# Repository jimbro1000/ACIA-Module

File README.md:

# HD6309SBC ACIA MODULE #

This design provides a standard RS232 capability to the
HD6309SBC board. Available baud rates range from 50 to
115200.

## Interface ##

The board utilises mapped IO at address #xx0C to interact
with the primary processor. The R65C51 uart provides four
registers starting at this address.

The value of xx depends on the "mapped memory" signal line,
by default this is $FF00.

## Notes ##

The intended clock speed of the main SBC board is just over
3MHz which exceeds the limits of the original R65C51.
A slower clock speed would facilitate the use of the Rockwell
made components but it is highly recommended to use the WDC
version which will operate at much higher clock frequencies
(higher than the main clock can supply)

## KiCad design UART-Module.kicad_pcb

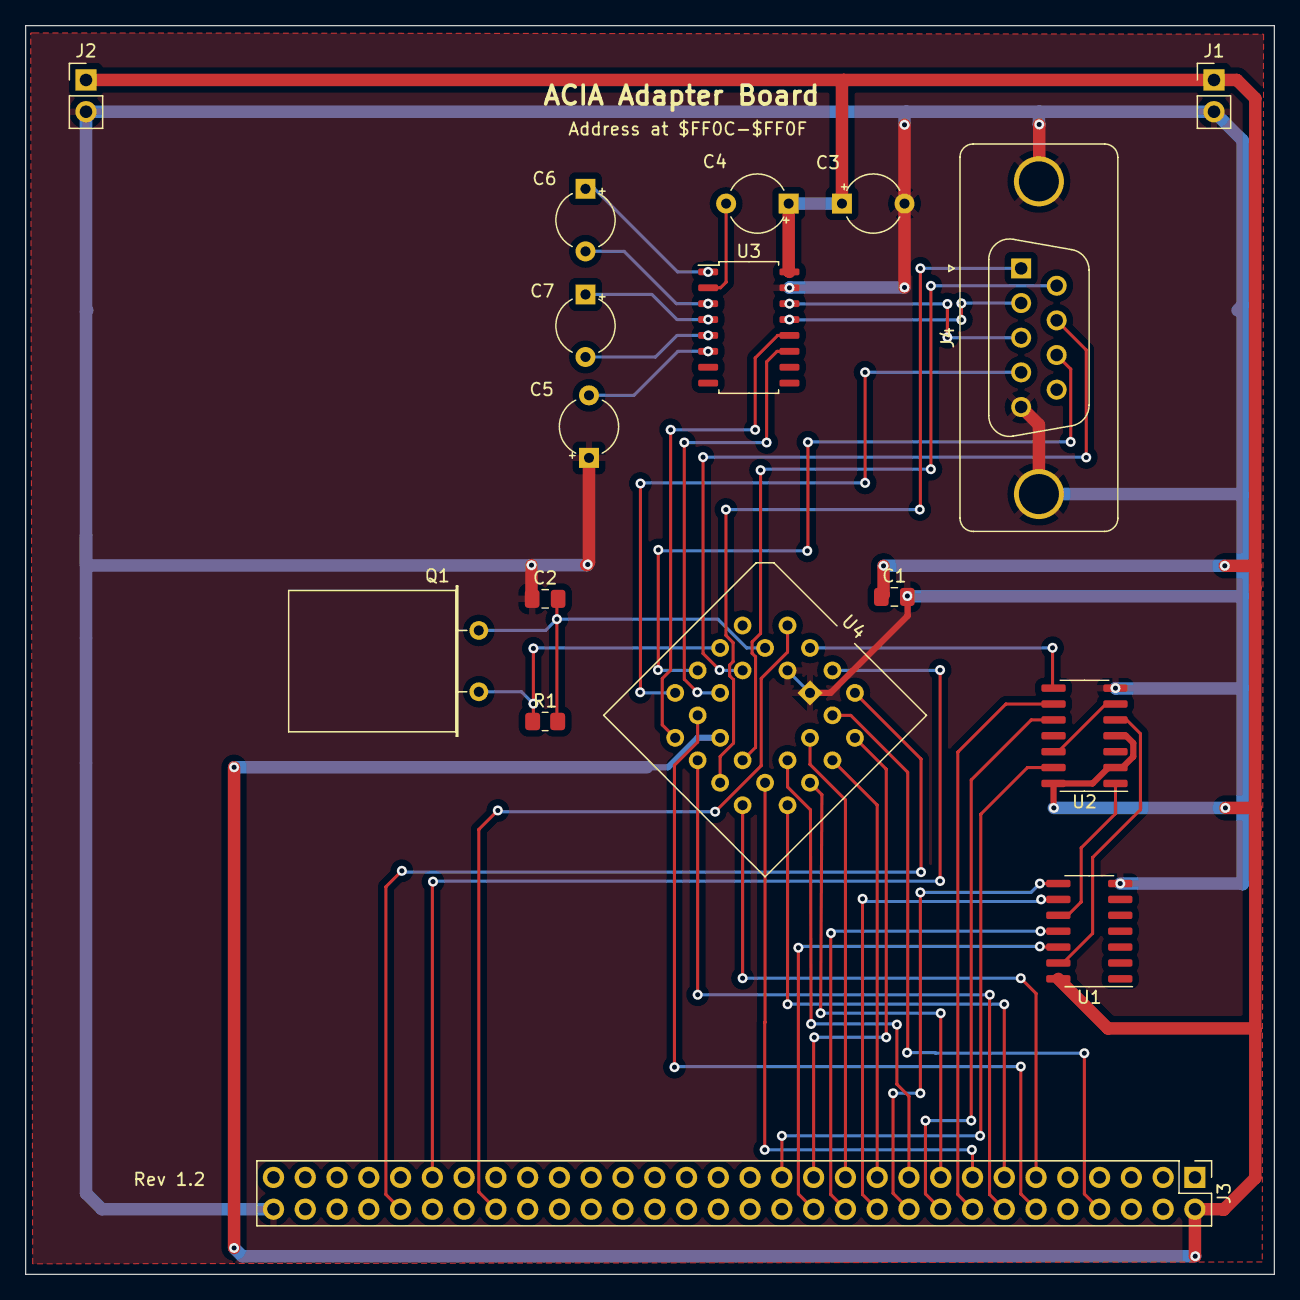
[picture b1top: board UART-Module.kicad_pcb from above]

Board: 2 copper layers, 99.8 x 99.8 mm, 17 parts (0 on the bottom side), 44 nets.

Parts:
C1: 1uF; C_0805_2012Metric_Pad1.18x1.45mm_HandSolder
C2: 30pF; C_0805_2012Metric_Pad1.18x1.45mm_HandSolder
C3, C4, C5, C6, C7: 0.1uF; CP_Radial_Tantal_D4.5mm_P5.00mm
J1, J2: Conn_01x02_Male; PinHeader_1x02_P2.54mm_Vertical
J3: Conn_02x30_Odd_Even; PinHeader_2x30_P2.54mm_Vertical
J4: DE9_Receptacle_MountingHoles; DSUB-9_Female_Vertical_P2.77x2.84mm_MountingHoles
Q1: 1.8432; Crystal_HC18-U_Horizontal
R1: 1M; R_0805_2012Metric_Pad1.20x1.40mm_HandSolder
U1: 74HC02; SO-14_3.9x8.65mm_P1.27mm
U2: 74HC21; SO-14_3.9x8.65mm_P1.27mm
U3: MAX232ID; SOIC-16_4.55x10.3mm_P1.27mm
U4: R65C51; PLCC-28_THT-Socket

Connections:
+5V: C1.1, C3.1, C4.1, J1.1, J2.1, J3.2, U1.14 (VCC), U2.2, U2.4, U2.14 (VCC), U3.16 (VCC), U4.15 (VCC)
A0: J3.12, U4.13 (RS0)
A1: J3.14, U4.14 (RS1)
A2: J3.16, U2.9
A3: J3.18, U2.10
A4: J3.20, U1.8
A5: J3.22, U1.9
A6: J3.24, U1.11
A7: J3.26, U1.12
CS0: U2.8, U4.2 (CS0)
D0: J3.11, U4.18 (D0)
D1: J3.13, U4.19 (D1)
D2: J3.15, U4.20 (D2)
D3: J3.17, U4.21 (D3)
D4: J3.19, U4.22 (D4)
D5: J3.21, U4.23 (D5)
D6: J3.23, U4.24 (D6)
D7: J3.25, U4.25 (D7)
E: J3.8, U4.27 (phi2)
GND: C1.2, C2.1, C3.2, C5.1, J1.2, J2.2, J3.60, J4.0 (PAD), J4.5, U1.7 (GND), U2.7 (GND), U3.15 (GND), U4.1 (VSS), U4.3 (~CS1)
MAPPED_MEM: J3.27, U2.13
unnamed: U1.10, U2.1
unnamed: U1.13, U2.5
unnamed: U2.6, U2.12
unnamed: C6.1, U3.1 (C1+)
unnamed: C6.2, U3.3 (C1-)
unnamed: C7.1, U3.4 (C2+)
unnamed: C7.2, U3.5 (C2-)
unnamed: C4.2, U3.2 (VS+)
unnamed: C5.2, U3.6 (VS-)
RxD: U3.12 (R1OUT), U4.12 (RxD)
RxDv: J4.2, U3.13 (R1IN)
R/~W: J3.49, U4.28 (R/~W)
TxD: U3.11 (T1IN), U4.10 (TxD)
TxDv: J4.3, U3.14 (T1OUT)
XTLI: C2.2, Q1.1, R1.2, U4.6 (XTLI)
XTLO: Q1.2, R1.1, U4.7 (XTLO)
~CTS: J4.8, U4.9 (~CTS)
~DCD: J4.1, U4.16 (~DCD)
~DSR: J4.6, U4.17 (~DSR)
~DTR: J4.4, U4.11 (~DTR)
~IRQ: J3.52, U4.26 (~IRQ)
~RESET: J3.46, U4.4 (~RESET)
~RTS: J4.7, U4.8 (~RTS)

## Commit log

2023-04-10 revise components
2023-04-11 complete traces
2023-04-11 fix chip select
2023-04-21 add max232 for correct serial voltages
2023-05-02 fix footprint for U3
